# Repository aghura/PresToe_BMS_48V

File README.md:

# PresToe_BMS_48V
Battery Management System for PresToe Robot

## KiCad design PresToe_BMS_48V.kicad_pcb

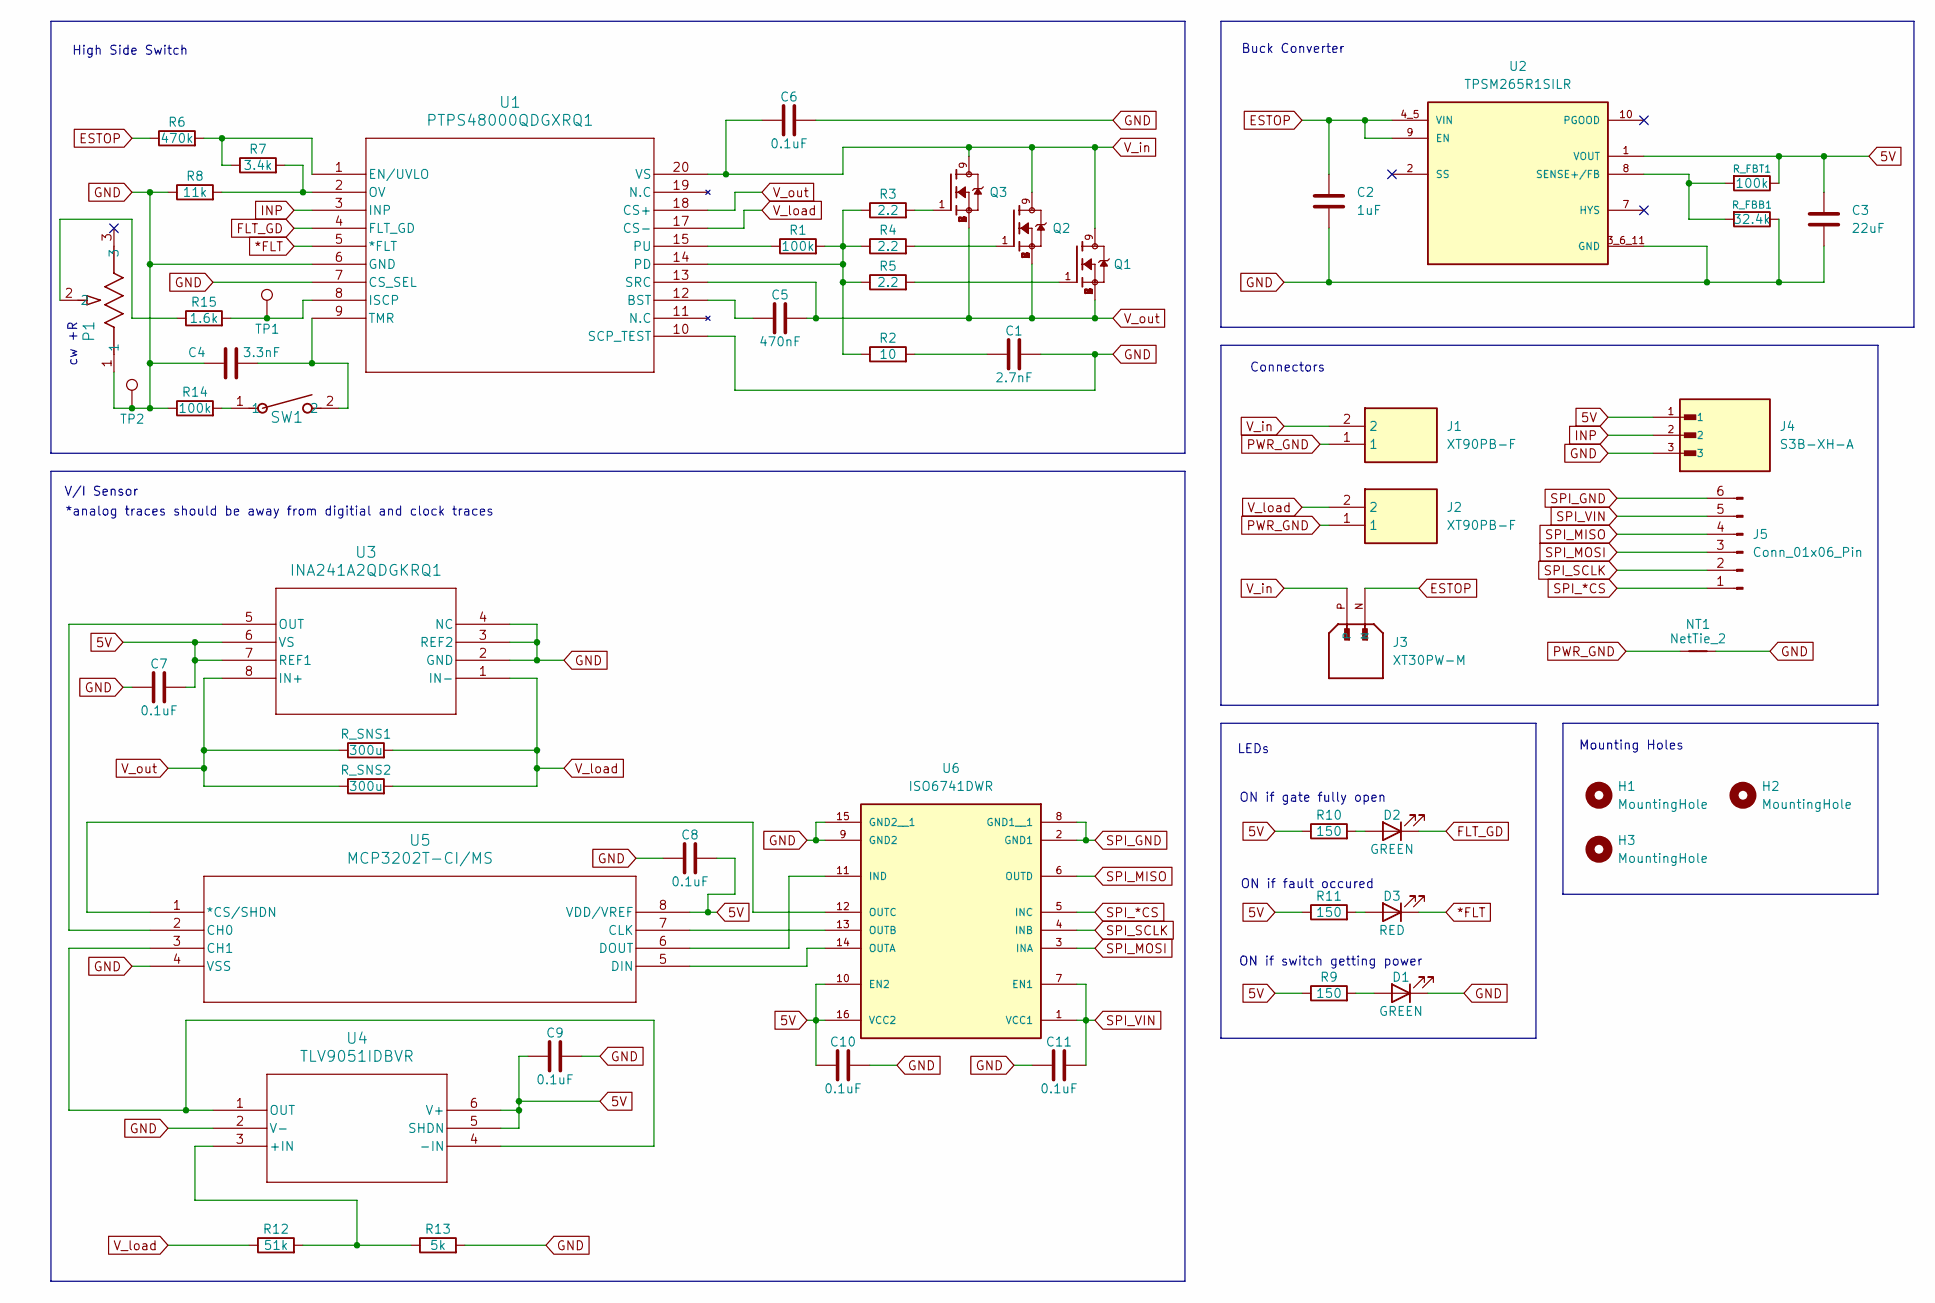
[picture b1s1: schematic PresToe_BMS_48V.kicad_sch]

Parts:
C1: 2.7nF; C_0603_1608Metric
C2: 1uF; C_0805_2012Metric
C3: 22uF; C_1210_3225Metric
C4: 3.3nF; C_0603_1608Metric
C5: 470nF; C_0603_1608Metric
C6, C7, C8, C9, C10, C11: 0.1uF; C_0603_1608Metric
D1, D2: GREEN; LED_0603_1608Metric
D3: RED; LED_0603_1608Metric
H1, H2, H3: MountingHole; MountingHole_3.2mm_M3_Pad_Via
J1, J2: XT90PB-F; XT90PBF; Manufacturer_Part_Number XT90PB-F
J3: XT30PW-M; AMASS_XT30PW-M; PARTREV 1.2
J4: S3B-XH-A; JST_S3B-XH-A
J5: Conn_01x06_Pin; JST_EH_S6B-EH_1x06_P2.50mm_Horizontal
NT1: NetTie_2; NetTie-2_SMD_Pad2.0mm
P1: T93YA203JT20; RES3_89P_TTE
Q1, Q2, Q3: IAUS200N08S5N023ATMA1; TRANS_IAUS200N08S5N023ATMA1
R1, R14: 100k; R_0603_1608Metric
R2: 10; R_0603_1608Metric
R3, R4, R5: 2.2; R_0603_1608Metric
R6: 470k; R_0603_1608Metric
R7: 3.4k; R_0603_1608Metric
R8: 11k; R_0603_1608Metric
R9, R10, R11: 150; R_0603_1608Metric
R12: 51k; R_0603_1608Metric
R13: 5k; R_0603_1608Metric
R15: 1.6k; R_0603_1608Metric
R_FBB1: 32.4k; R_0603_1608Metric
R_FBT1: 100k; R_0603_1608Metric
R_SNS1, R_SNS2: 300u; Custom_R_300u
SW1: DS04-254-1-01BK-SMT; SW_DS04-254_CUD
TP1, TP2: TestPoint; TestPoint_Pad_D2.0mm
U1: PTPS48000QDGXRQ1; VSSOP19-DGX_TEX
U2: TPSM265R1SILR; MODULE_TPSM265R1SILR; PARTREV B
U3: INA241A2QDGKRQ1; VSSOP8_DGK_TEX
U4: TLV9051IDBVR; SOT23_DBV_TEX
U5: MCP3202T-CI/MS; SOIC8-N_MC_MCH
U6: ISO6741DWR; SOIC127P1030X265-16N; PARTREV G

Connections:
5V: C3.1, C7.2, C8.2, C9.1, C10.1, J4.1, R9.1, R10.1, R11.1, R_FBT1.1, U2.1 (VOUT), U3.6 (VS), U3.7 (REF1), U4.5 (SHDN), U4.6 (V+), U5.8 (VDD/VREF), U6.10 (EN2), U6.16 (VCC2)
*FLT: D3.1 (C), U1.5 (*FLT)
ESTOP: C2.1, J3.N, R6.1, U2.4_5 (VIN), U2.9 (EN)
FLT_GD: D2.1 (C), U1.4 (FLT_GD)
GND: C1.1, C2.2, C3.2, C4.1, C6.2, C7.1, C8.1, C9.2, C10.2, C11.1, D1.1 (C), J4.3, NT1.2, P1.1, R8.1, R13.2, R14.1, R_FBB1.1, TP2.1, U1.6 (GND), U1.7 (CS_SEL), U1.10 (SCP_TEST), U2.3_6_11 (GND), U3.2 (GND), U3.3 (REF2), U3.4 (NC), U4.2 (V-), U5.4 (VSS), U6.9 (GND2), U6.15 (GND2__1)
INP: J4.2, U1.3 (INP)
unnamed: C1.2, R2.2
unnamed: D1.2 (A), R9.2
unnamed: D2.2 (A), R10.2
unnamed: D3.2 (A), R11.2
unnamed: P1.2, R15.1
unnamed: Q1.1, R5.2
unnamed: Q2.1, R4.2
unnamed: Q3.1, R3.2
unnamed: R14.2, SW1.1
unnamed: C5.2, U1.12 (BST)
unnamed: R6.2, R7.1, U1.1 (EN/UVLO)
unnamed: R15.2, TP1.1, U1.8 (ISCP)
unnamed: R7.2, R8.2, U1.2 (OV)
unnamed: R1.2, R2.1, R3.1, R4.1, R5.1, U1.14 (PD)
unnamed: R1.1, U1.15 (PU)
unnamed: C4.2, SW1.2, U1.9 (TMR)
unnamed: R_FBB1.2, R_FBT1.2, U2.8 (SENSE+/FB)
unnamed: U3.5 (OUT), U5.2 (CH0)
unnamed: R12.2, R13.1, U4.3 (+IN)
unnamed: U4.1 (OUT), U4.4 (-IN), U5.3 (CH1)
unnamed: U5.1 (*CS/SHDN), U6.12 (OUTC)
unnamed: U5.7 (CLK), U6.13 (OUTB)
unnamed: U5.5 (DIN), U6.14 (OUTA)
unnamed: U5.6 (DOUT), U6.11 (IND)
PWR_GND: J1.1, J2.1, NT1.1
SPI_*CS: J5.1, U6.5 (INC)
SPI_GND: J5.6, U6.2 (GND1), U6.8 (GND1__1)
SPI_MISO: J5.4, U6.6 (OUTD)
SPI_MOSI: J5.3, U6.3 (INA)
SPI_SCLK: J5.2, U6.4 (INB)
SPI_VIN: C11.2, J5.5, U6.1 (VCC1), U6.7 (EN1)
V_in: C6.1, J1.2, J3.P, Q1.9, Q2.9, Q3.9, U1.20 (VS)
V_load: J2.2, R12.1, R_SNS1.2, R_SNS2.2, U1.17 (CS-), U3.1 (IN-)
V_out: C5.1, Q1.2, Q1.3, Q1.4, Q1.5, Q1.6, Q1.7, Q1.8, Q2.2, Q2.3, Q2.4, Q2.5, Q2.6, Q2.7, Q2.8, Q3.2, Q3.3, Q3.4, Q3.5, Q3.6, Q3.7, Q3.8, R_SNS1.1, R_SNS2.1, U1.13 (SRC), U1.18 (CS+), U3.8 (IN+)

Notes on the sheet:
LEDs
Connectors
Buck Converter
Mounting Holes
*analog traces should be away from digitial and clock traces
ON if switch getting power
ON if fault occured
High Side Switch
V/I Sensor
cw +R
ON if gate fully open

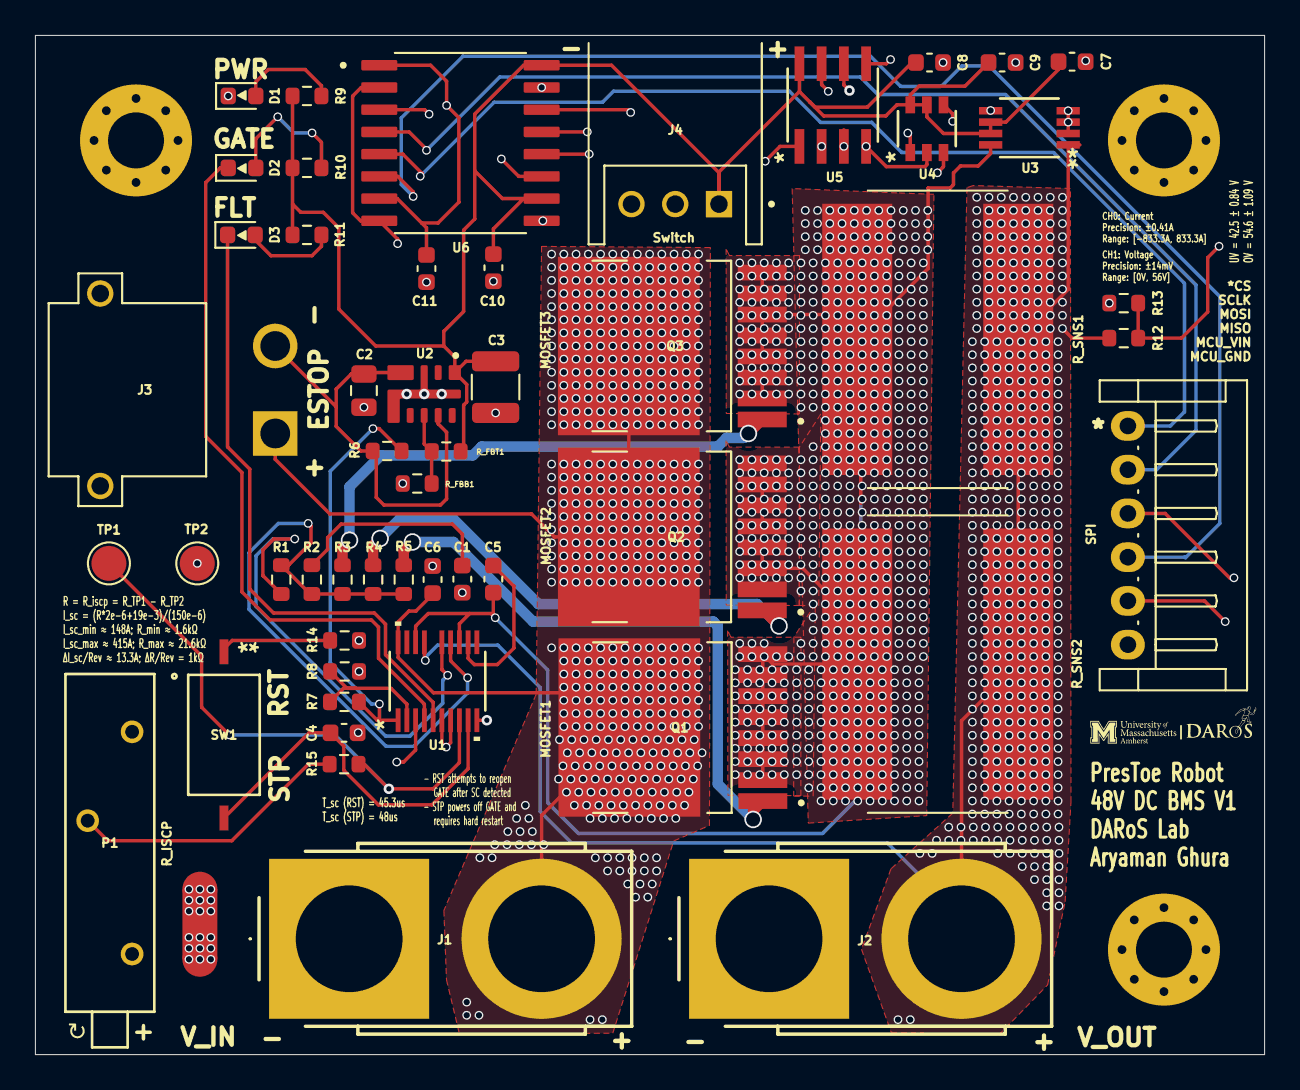
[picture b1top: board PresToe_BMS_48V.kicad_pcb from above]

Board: 6 copper layers, 70.2 x 58.2 mm, 55 parts (0 on the bottom side), 40 nets.

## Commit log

2025-07-17 Finalized Schematic
    High Side Switch, Current/Voltage Sensor with Isolated 12bit ADC/SPI, Buck Converter for 5V Rail, OV/UV protection, SC protection with modifiable current limit and retry timer, in-rush limit to 100A,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
2025-07-18 Basic footprint layout added
2025-07-22 finalized, remaining final checks
2025-07-23 fixed bugs, finalized design
2025-07-24 Finalized V1
2025-08-10 gerber files, supporting data
